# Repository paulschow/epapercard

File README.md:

# epapercard
Design for a epaper business card

Project writeup http://www.paulschow.com/2016/08/epaper-business-card.html

Based on the reference deisgns from http://repaper.org/

Requires MSP430 Launchpad to program.

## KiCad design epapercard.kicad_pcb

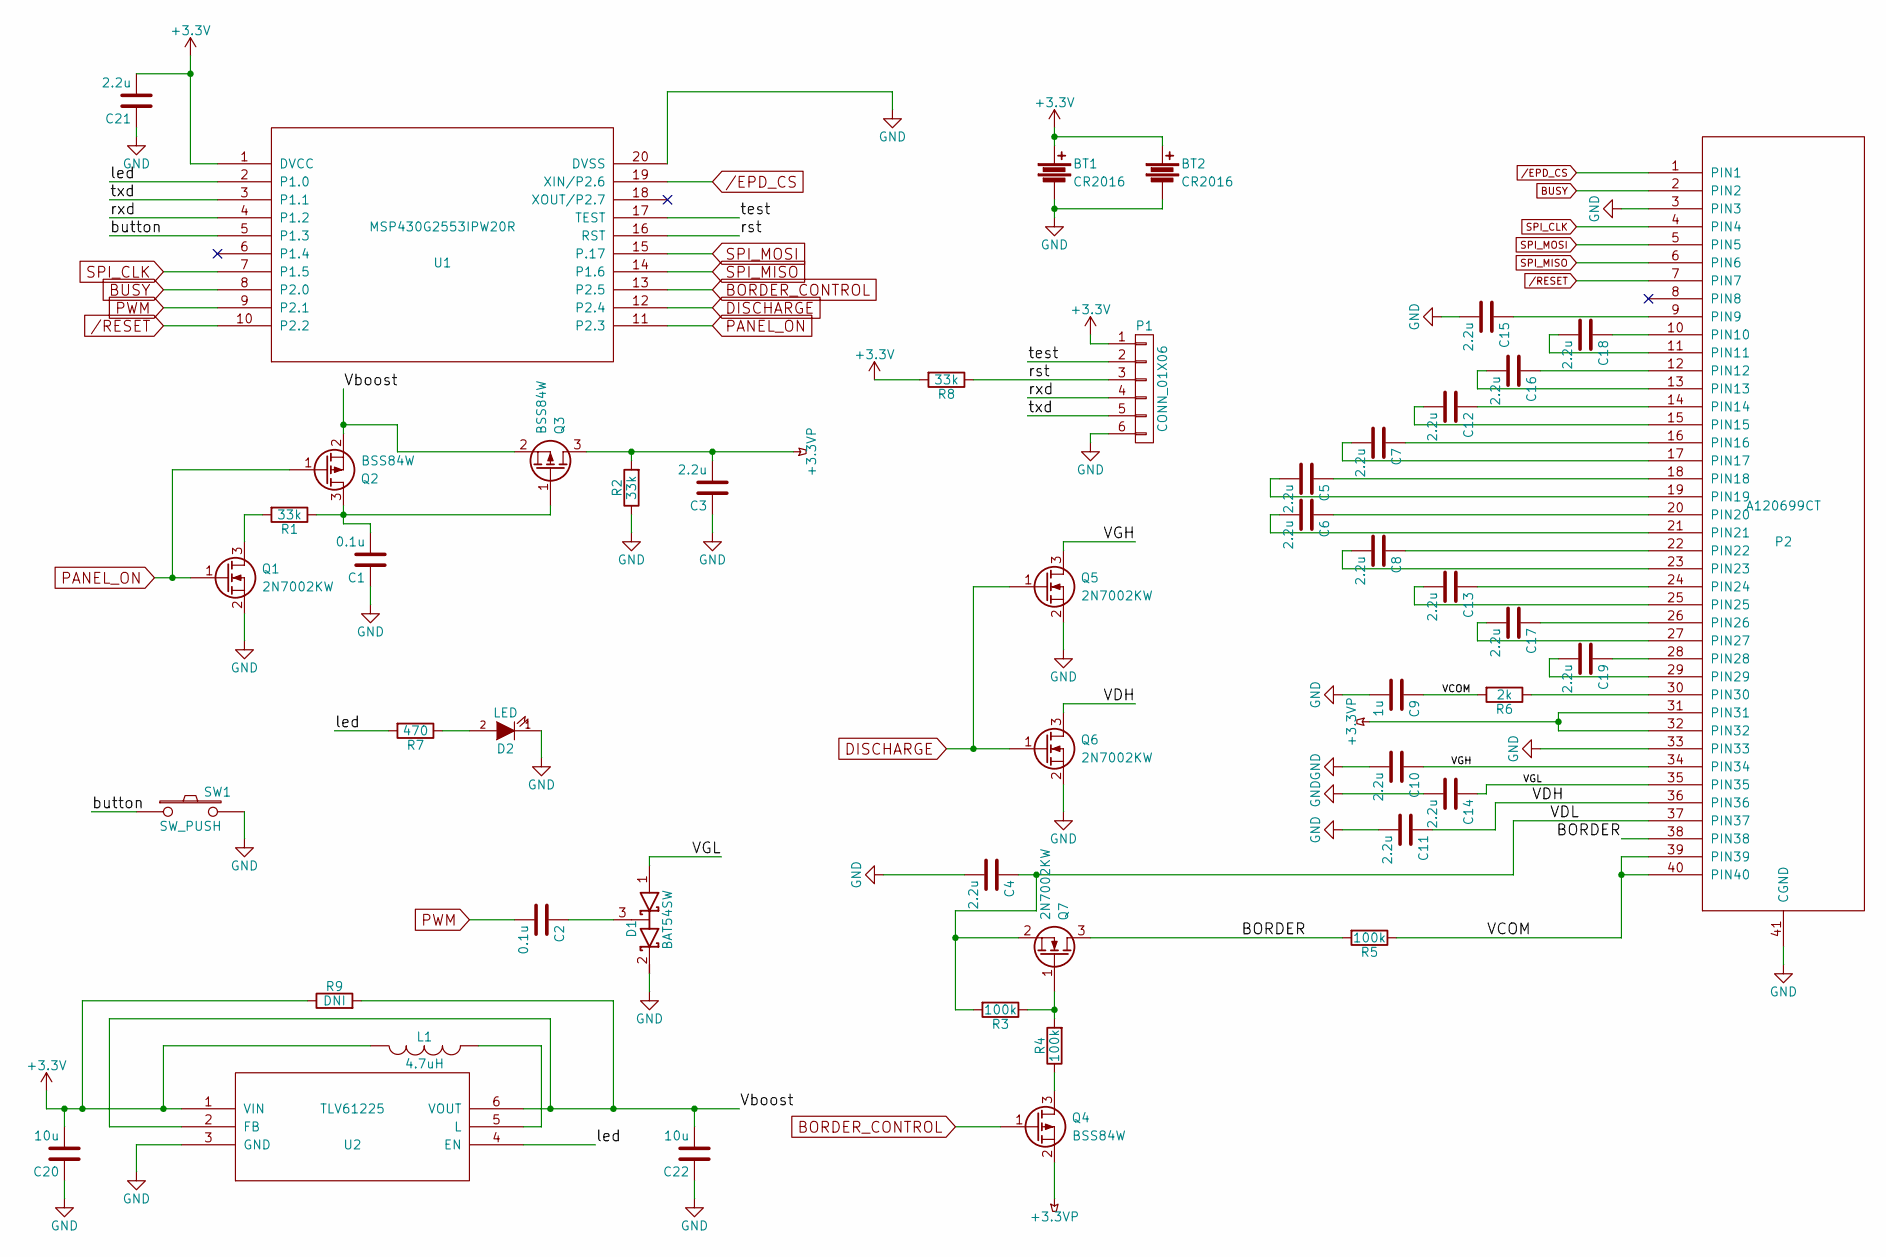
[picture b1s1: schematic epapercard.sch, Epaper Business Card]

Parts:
BT1: CR2016; CR2016sm-F2N
BT2: CR2016; CR2032sm
C1, C2: 0.1u; C_0805_HandSoldering
C3, C4, C5, C6, C7, C8, C10, C11, C12, C13, C14, C15, C16, C17, C18, C19, C21: 2.2u; C_0805_HandSoldering
C9: 1u; C_0805_HandSoldering
C20, C22: 10u; C_0805_HandSoldering
D1: BAT54SW; SOT-323
D2: LED; C_0805_HandSoldering
L1: 4.7uH; Inductor_1212
P1: CONN_01X06; Pin_Header_Straight_1x06
P2: A120699CT
Q1, Q5, Q6, Q7: 2N7002KW; SOT-323
Q2, Q3, Q4: BSS84W; SOT-323
R1, R2, R8: 33k; R_0805_HandSoldering
R3, R4, R5: 100k; R_0805_HandSoldering
R6: 2k; R_0805_HandSoldering
R7: 470; R_0805_HandSoldering
R9: DNI; R_0201
SW1: SW_PUSH; SW_SPST_EVPBF
U1: MSP430G2553IPW20R; TSSOP-20_4.4x6.5mm_Pitch0.65mm
U2: TLV61225; SOT-23-6

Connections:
+3.3VP: C3.2, P2.31 (PIN31), P2.32 (PIN32), Q3.3 (D), Q4.2 (S), R2.2
+3V3: BT1.1, BT2.1, C20.2, C21.2, L1.1, P1.1, R8.2, R9.1, U1.1 (DVCC), U2.1 (VIN)
/BORDER: P2.38 (PIN38), Q7.3 (D), R5.2
/EPD_CS: P2.1 (PIN1), U1.19 (XIN/P2.6)
/RESET: P2.7 (PIN7), U1.10 (P2.2)
/VCOM: C9.1, P2.39 (PIN39), P2.40 (PIN40), R5.1, R6.2
/VDH: C11.1, P2.36 (PIN36), Q6.3 (D)
/VDL: C4.1, P2.37 (PIN37), Q7.2 (S), R3.2
/VGH: C10.1, P2.34 (PIN34), Q5.3 (D)
/VGL: C14.1, D1.1 (A), P2.35 (PIN35)
/Vboost: C22.2, Q2.2 (S), Q3.2 (S), R9.2, U2.2 (FB), U2.6 (VOUT)
/button: SW1.1, U1.5 (P1.3)
/led: R7.2, U1.2 (P1.0), U2.4 (EN)
/rst: P1.3, R8.1, U1.16 (RST)
/rxd: P1.4, U1.4 (P1.2)
/test: P1.2, U1.17 (TEST)
/txd: P1.5, U1.3 (P1.1)
BORDER_CONTROL: Q4.1 (G), U1.13 (P2.5)
BUSY: P2.2 (PIN2), U1.8 (P2.0)
DISCHARGE: Q5.1 (G), Q6.1 (G), U1.12 (P2.4)
GND: BT1.2, BT2.2, C1.1, C3.1, C4.2, C9.2, C10.2, C11.2, C14.2, C15.2, C20.1, C21.1, C22.1, D1.2 (K), D2.1 (K), P1.6, P2.3 (PIN3), P2.33 (PIN33), P2.41 (CGND), Q1.2 (S), Q5.2 (S), Q6.2 (S), R2.1, SW1.2, U1.20 (DVSS), U2.3 (GND)
unnamed: C1.2, Q2.3 (D), Q3.1 (G), R1.1
unnamed: C2.1, D1.3 (common)
unnamed: C5.1, P2.18 (PIN18)
unnamed: C5.2, P2.19 (PIN19)
unnamed: C6.1, P2.20 (PIN20)
unnamed: C6.2, P2.21 (PIN21)
unnamed: C7.1, P2.16 (PIN16)
unnamed: C7.2, P2.17 (PIN17)
unnamed: C8.1, P2.22 (PIN22)
unnamed: C8.2, P2.23 (PIN23)
unnamed: C12.1, P2.14 (PIN14)
unnamed: C12.2, P2.15 (PIN15)
unnamed: C13.1, P2.24 (PIN24)
unnamed: C13.2, P2.25 (PIN25)
unnamed: C15.1, P2.9 (PIN9)
unnamed: C16.1, P2.12 (PIN12)
unnamed: C16.2, P2.13 (PIN13)
unnamed: C17.1, P2.26 (PIN26)
unnamed: C17.2, P2.27 (PIN27)
unnamed: C18.1, P2.10 (PIN10)
unnamed: C18.2, P2.11 (PIN11)
unnamed: C19.1, P2.28 (PIN28)
unnamed: C19.2, P2.29 (PIN29)
unnamed: D2.2 (A), R7.1
unnamed: L1.2, U2.5 (L)
unnamed: P2.30 (PIN30), R6.1
unnamed: Q1.3 (D), R1.2
unnamed: Q4.3 (D), R4.1
unnamed: Q7.1 (G), R3.1, R4.2
PANEL_ON: Q1.1 (G), Q2.1 (G), U1.11 (P2.3)
PWM: C2.2, U1.9 (P2.1)
SPI_CLK: P2.4 (PIN4), U1.7 (P1.5)
SPI_MISO: P2.6 (PIN6), U1.14 (P1.6)
SPI_MOSI: P2.5 (PIN5), U1.15 (P.17)

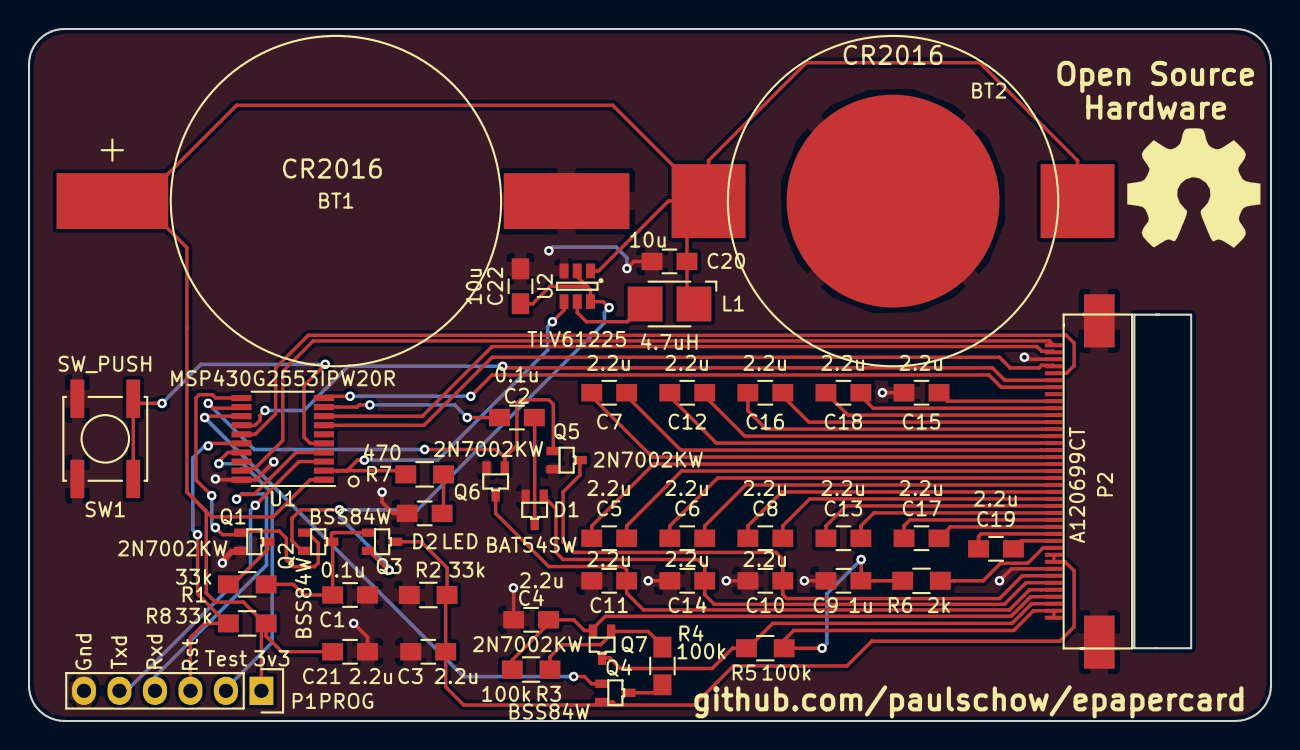
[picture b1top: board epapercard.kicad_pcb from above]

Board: 2 copper layers, 88.9 x 49.5 mm, 47 parts (0 on the bottom side), 55 nets.

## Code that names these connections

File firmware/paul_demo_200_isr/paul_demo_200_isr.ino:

// Demo code for epapercard
// by Paul Schow
// https://github.com/paulschow/epapercard
// Switches between two images on button press
// Based on demo_200.ino by Pervasive Displays, Inc.
// Original copyright statement below

// Copyright 2013-2015 Pervasive Displays, Inc.
//
// Licensed under the Apache License, Version 2.0 (the "License");
// you may not use this file except in compliance with the License.
// You may obtain a copy of the License at:
//
//   http://www.apache.org/licenses/LICENSE-2.0
//
// Unless required by applicable law or agreed to in writing,
// software distributed under the License is distributed on an
// "AS IS" BASIS, WITHOUT WARRANTIES OR CONDITIONS OF ANY KIND, either
// express or implied.  See the License for the specific language
// governing permissions and limitations under the License.


#if defined(ENERGIA)
#include <Energia.h>
#else
#include <Arduino.h>
#endif

#include <inttypes.h>
#include <ctype.h>

// required libraries
#include <SPI.h>
//#include <EPD_FLASH.h>
//#include <EPD_V110_G1.h>
#include <EPD_V231_G2.h>
#define SCREEN_SIZE 200
#include <EPD_PANELS.h>
#include <EPD_PINOUT.h>

// select two images from:  text_image text-hello cat aphrodite venus saturn
#define IMAGE_1  text_hello
#define IMAGE_2  saturn

// Error message for MSP430
//#if (SCREEN_SIZE == 270) && defined(__MSP430G2553__)
//#error MSP430: not enough memory
//#endif

// no futher changed below this point

// current version number
#define DEMO_VERSION "5"

// pre-processor convert to string
#define MAKE_STRING1(X) #X
#define MAKE_STRING(X) MAKE_STRING1(X)

// other pre-processor magic
// token joining and computing the string for #include
#define ID(X) X
#define MAKE_NAME1(X,Y) ID(X##Y)
#define MAKE_NAME(X,Y) MAKE_NAME1(X,Y)
#define MAKE_JOIN(X,Y) MAKE_STRING(MAKE_NAME(X,Y))

// calculate the include name and variable names
#define IMAGE_1_FILE MAKE_JOIN(IMAGE_1,EPD_IMAGE_FILE_SUFFIX)
#define IMAGE_1_BITS MAKE_NAME(IMAGE_1,EPD_IMAGE_NAME_SUFFIX)
#define IMAGE_2_FILE MAKE_JOIN(IMAGE_2,EPD_IMAGE_FILE_SUFFIX)
#define IMAGE_2_BITS MAKE_NAME(IMAGE_2,EPD_IMAGE_NAME_SUFFIX)

// Add Images library to compiler path
#include <Images.h>  // this is just an empty file

// images
PROGMEM const
#define unsigned
#define char uint8_t
#include IMAGE_1_FILE
#undef char
#undef unsigned

PROGMEM const
#define unsigned
#define char uint8_t
#include IMAGE_2_FILE
#undef char
#undef unsigned

// LED anode through resistor to I/O pin
// LED cathode to Ground
#define LED_ON  HIGH
#define LED_OFF LOW

// define the E-Ink display
EPD_Class EPD(EPD_SIZE,
          Pin_PANEL_ON,
          Pin_BORDER,
          Pin_DISCHARGE,
#if EPD_PWM_REQUIRED
          Pin_PWM,
#endif
          Pin_RESET,
          Pin_BUSY,
          Pin_EPD_CS);




// I/O setup
void setup() {

#if EPD_PWM_REQUIRED
    pinMode(Pin_PWM, OUTPUT);
#endif
    pinMode(Pin_BUSY, INPUT);
    pinMode(Pin_RESET, OUTPUT);
    pinMode(Pin_PANEL_ON, OUTPUT);
    pinMode(Pin_DISCHARGE, OUTPUT);
    pinMode(Pin_BORDER, OUTPUT);
    pinMode(Pin_EPD_CS, OUTPUT);
    //pinMode(Pin_EPD_FLASH_CS, OUTPUT);

#if EPD_PWM_REQUIRED
    digitalWrite(Pin_PWM, LOW);
#endif
    digitalWrite(Pin_RESET, LOW);
    digitalWrite(Pin_PANEL_ON, LOW);
    digitalWrite(Pin_DISCHARGE, LOW);
    digitalWrite(Pin_BORDER, LOW);
    digitalWrite(Pin_EPD_CS, LOW);
    //digitalWrite(Pin_EPD_FLASH_CS, HIGH);
    
    pinMode(Pin_RED_LED, OUTPUT);
  
    pinMode(P1_3, INPUT_PULLUP); // Attach pullup to 1.3 (button)
    attachInterrupt(P1_3, awake, FALLING); // Attach falling interrupt to 1.3
}


static int state = 1;


// main loop
void loop() {
  digitalWrite(Pin_RED_LED, LED_ON);
  changeimage(); // Change the picture
  digitalWrite(Pin_RED_LED, LED_OFF);
  suspend(); // Enter low power mode 4 (0.1uA)
}


void changeimage(){
    int temperature = 40; // set temp to 40 for faster changing
    EPD.begin(); // power up the EPD panel
    EPD.setFactor(temperature); // adjust for current temperature
    int delay_counts = 0;
    switch(state) {
    default:

    case 1:         // clear -> text
#if EPD_IMAGE_ONE_ARG
        EPD.image(IMAGE_1_BITS);
#elif EPD_IMAGE_TWO_ARG
        EPD.image_0(IMAGE_1_BITS);
#else
#error "unsupported image function"
#endif
        ++state;
        break;

    case 2:         // text -> picture
#if EPD_IMAGE_ONE_ARG
        EPD.image(IMAGE_2_BITS);
#elif EPD_IMAGE_TWO_ARG
        EPD.image(IMAGE_1_BITS, IMAGE_2_BITS);
#else
#error "unsupported image function"
#endif
        ++state;
        break;

    case 3:        // picture -> text
#if EPD_IMAGE_ONE_ARG
        EPD.image(IMAGE_1_BITS);
#elif EPD_IMAGE_TWO_ARG
        EPD.image(IMAGE_2_BITS, IMAGE_1_BITS);
#else
#error "unsupported image function"
#endif
        state = 2;  // back to picture next time
        break;
    }
    EPD.end();   // power down the EPD panel  
  
}

// interrupt service routine
void awake(void)
{
  wakeup(); // wakeup from lpm4
}

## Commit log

2016-05-12 Adding new parts
2016-05-12 Microcontroller connections
2016-05-12 Added charge pump caps
2016-05-12 Changed to Cern OHL
2016-05-12 Drew an amazing 2N7002
2016-05-12 I figure out how to use kicad again
2016-05-12 Change to CC-BY-SA-4.0 to match original license
2016-05-12 Fixed a few mistakes
2016-05-12 Added power circuit
2016-05-12 Fixed some labels
2016-05-13 Added programming circuit
2016-05-13 Attached footprints
2016-05-13 Laying board out
2016-05-13 I remembered how mirrors work
2016-05-13 Switched to surface mount battery holders
2016-05-13 Minor tweaks
2016-05-13 Connected everything
2016-05-13 Fixed silk
2016-05-13 More silk changes
2016-05-13 Added OSHW logo
2016-05-13 Generated gerbers
2016-05-13 Updated silk
2016-05-13 New gerbers
2016-05-16 Generated BOM
2016-05-27 Changed fet position
2016-05-31 Fixed pin numbering
2016-05-31 Adjusting footprints
2016-05-31 Extended ground pads
2016-05-31 Basically starting over
2016-05-31 Routed caps
2016-05-31 Placed all components
2016-05-31 All routed
2016-06-04 New BOM
2016-06-04 Added digikey part numbers
2016-06-12 Adding firmware
2016-06-12 Moving code around
2016-06-17 Updated working firmware w/o interrupts
2016-07-06 Removed extra code
2016-07-06 Low power mode interrupt working
2016-07-06 Added comments
2016-07-06 Adding use information
2016-07-06 Added LED back
2016-07-06 Added CR2016 footprint
2016-07-06 Changed battery footprint
2016-07-06 Adjusted dimensions
2016-07-07 Added boost regulator
2016-07-13 Changing CR2016 footprint to one with tabs
2016-07-13 Add tabbed battery and boost reg
2016-07-13 Move a few tracks around
2016-07-13 Everything connected
2016-07-13 Silk cleanup
2016-08-01 Adding libraries
2016-08-05 Fixed TLV61225 footprint
2016-08-14 Fixed boost regulator
2016-08-14 Generate BOM
2016-08-14 Updated BOMs
2016-08-14 Make github happy
2016-08-14 Updated BOM
2016-08-14 Added schematic and board pictures
2016-08-17 Adding writeup link
2016-09-15 Move library files, enable four images
2016-09-15 Remove old libraries
